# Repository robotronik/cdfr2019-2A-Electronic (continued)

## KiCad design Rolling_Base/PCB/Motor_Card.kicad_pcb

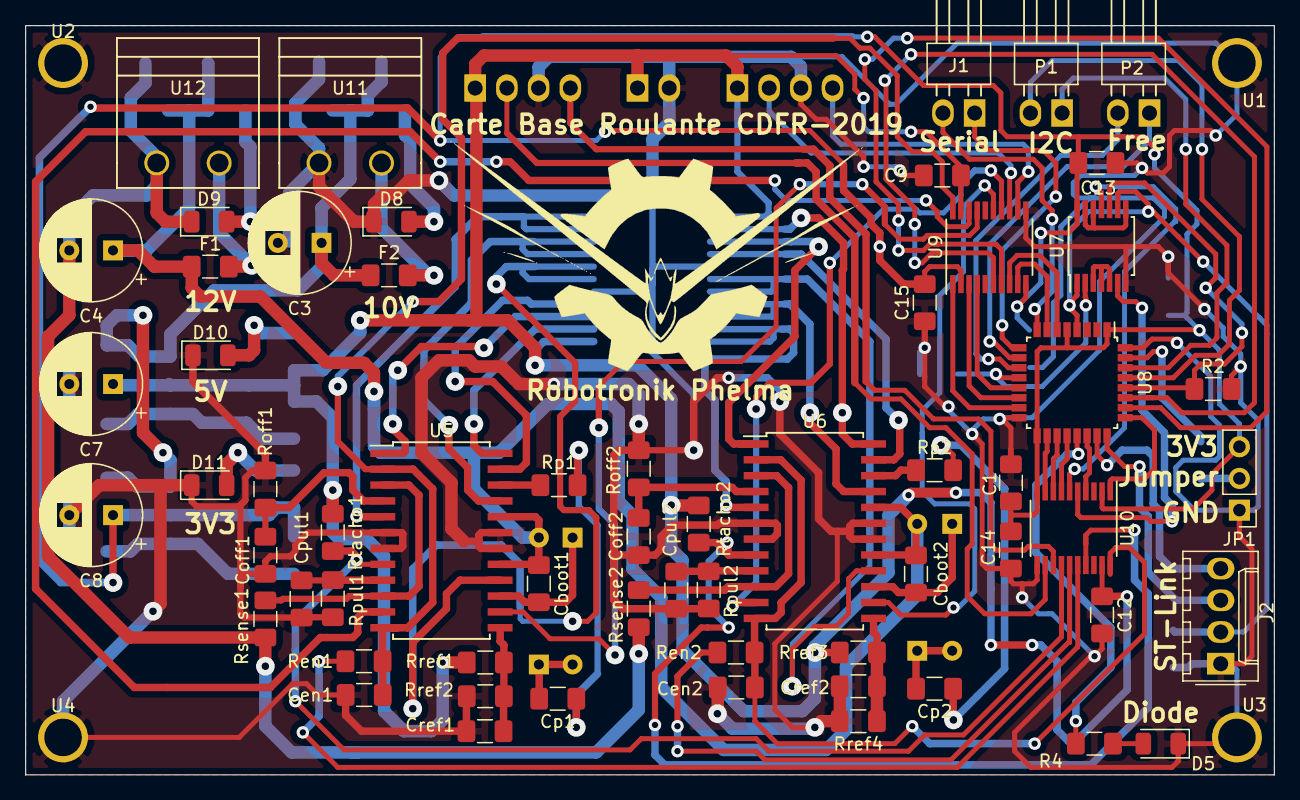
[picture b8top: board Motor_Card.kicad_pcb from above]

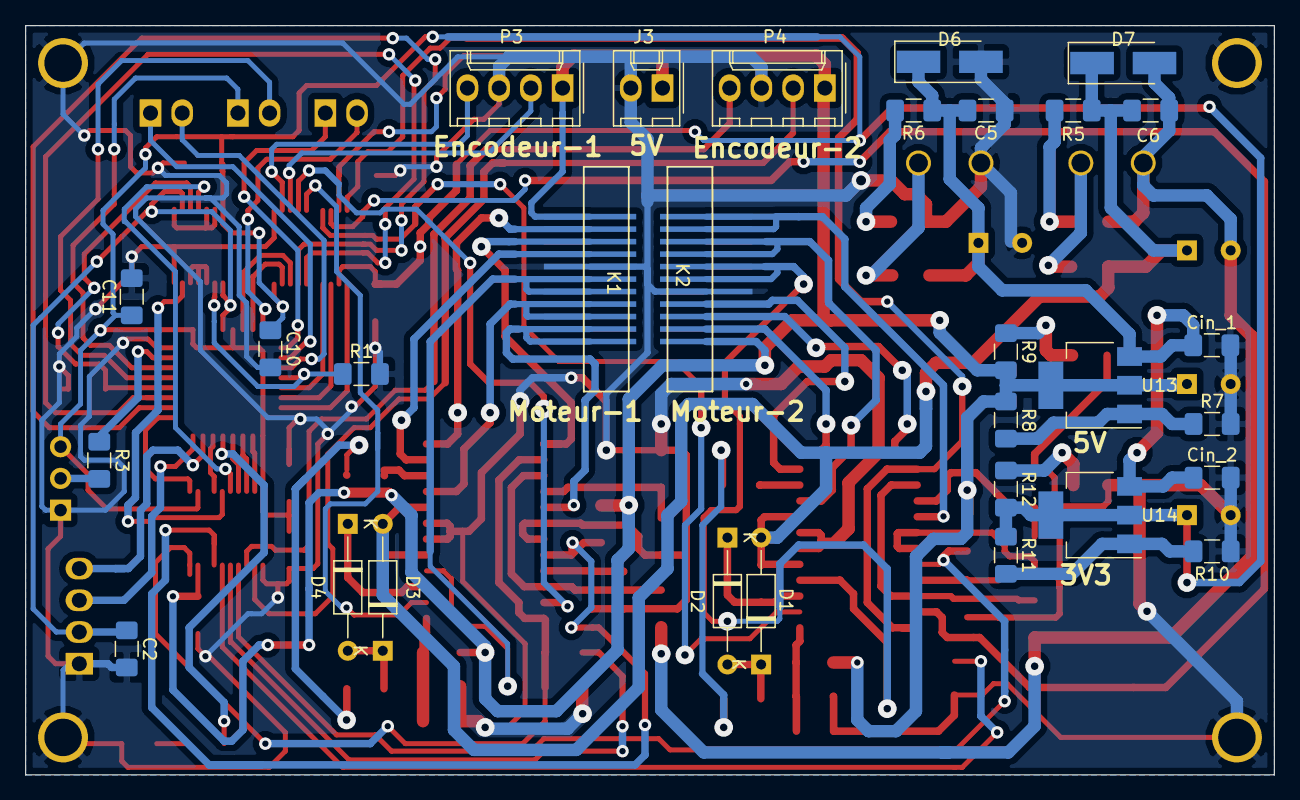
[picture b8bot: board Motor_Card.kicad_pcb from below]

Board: 2 copper layers, 100.0 x 60.0 mm, 94 parts (30 on the bottom side), 87 nets.

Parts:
C1, C2, C5, C6, C13, C14, C15: 100n; C_1206_3216Metric_Pad1.42x1.75mm_HandSolder
C3, C4: 100u; CP_Radial_D8.0mm_P3.50mm
C7, C8: 10u; CP_Radial_D8.0mm_P3.50mm
C9, C10, C11, C12: 0,1u; C_1206_3216Metric_Pad1.42x1.75mm_HandSolder
Cboot1, Cboot2: 220n; C_1206_3216Metric_Pad1.42x1.75mm_HandSolder
Cen1, Cen2: 5.6n; C_1206_3216Metric_Pad1.42x1.75mm_HandSolder
Cin_1, Cin_2: 0,1u; C_1206_3216Metric_Pad1.42x1.75mm_HandSolder
Coff1, Coff2: 1n; C_1206_3216Metric_Pad1.42x1.75mm_HandSolder
Cp1, Cp2: 10n; C_1206_3216Metric_Pad1.42x1.75mm_HandSolder
Cpul1, Cpul2: 10n; C_1206_3216Metric_Pad1.42x1.75mm_HandSolder
Cref1, Cref2: 10n; C_1206_3216Metric_Pad1.42x1.75mm_HandSolder
D1, D2, D3, D4: 1N4148; D_DO-35_SOD27_P10.16mm_Horizontal
D5, D9: LED_ALT; LED_1206_3216Metric
D6, D7: D_10A; D_SMA_Handsoldering
D8: LED_VCC; LED_1206_3216Metric
D10: LED_5V; LED_1206_3216Metric
D11: LED_3.3V; LED_1206_3216Metric
F1: Fuse_Puiss; Fuse_1206_3216Metric_Pad1.42x1.75mm_HandSolder
F2: Fuse_Num; Fuse_1206_3216Metric_Pad1.42x1.75mm_HandSolder
J1: CONN_SERIAL; Molex_KK-254_1x02_P2.54mm_Horizontal
J2: swdio; Molex_KK-254_AE-6410-04A_1x04_P2.54mm_Vertical
J3: FAN; Molex_KK-254_AE-6410-02A_1x02_P2.54mm_Vertical
JP1: Jumper_NC_Dual; PinHeader_1x03_P2.54mm_Vertical
K1, K2: Maxon-200142; Molex-52610-1133
P1: CONN_I2C; Molex_KK-254_1x02_P2.54mm_Horizontal
P2: CONN_FREE; Molex_KK-254_1x02_P2.54mm_Horizontal
P3: encoder_1; Molex_KK-254_AE-6410-04A_1x04_P2.54mm_Vertical
P4: encoder_2; Molex_KK-254_AE-6410-04A_1x04_P2.54mm_Vertical
R1, R2, R3: 10k; R_1206_3216Metric_Pad1.42x1.75mm_HandSolder
R4, R9, R12: 470; R_1206_3216Metric_Pad1.42x1.75mm_HandSolder
R5, R6: 2k; R_1206_3216Metric_Pad1.42x1.75mm_HandSolder
R7: 820; R_1206_3216Metric_Pad1.42x1.75mm_HandSolder
R8: 270; R_1206_3216Metric_Pad1.42x1.75mm_HandSolder
R10: 370; R_1206_3216Metric_Pad1.42x1.75mm_HandSolder
R11: 220; R_1206_3216Metric_Pad1.42x1.75mm_HandSolder
Ren1, Ren2: 100k; R_1206_3216Metric_Pad1.42x1.75mm_HandSolder
Roff1, Roff2: 33k; R_1206_3216Metric_Pad1.42x1.75mm_HandSolder
Rp1, Rp2: 100; R_1206_3216Metric_Pad1.42x1.75mm_HandSolder
Rpul1, Rpul2: 47k; R_1206_3216Metric_Pad1.42x1.75mm_HandSolder
Rref1, Rref3: 1.2k; R_1206_3216Metric_Pad1.42x1.75mm_HandSolder
Rref2, Rref4: 220; R_1206_3216Metric_Pad1.42x1.75mm_HandSolder
Rsense1, Rsense2: 0.3; R_1206_3216Metric_Pad1.42x1.75mm_HandSolder
Rtacho1, Rtacho2: 1k; R_1206_3216Metric_Pad1.42x1.75mm_HandSolder
U1, U2, U3, U4: Trou-3
U5, U6: L6235D; SOIC-24W_7.5x15.4mm_P1.27mm
U7: 74HC00; TSSOP-14_4.4x5mm_P0.65mm
U8: stm32f303k8t6; LQFP-32_7x7mm_P0.8mm
U9, U10: txb0108; TSSOP-20_4.4x6.5mm_P0.65mm
U11, U12: B_Plug_5mm; Bplug-5mm
U13, U14: LM317_SOT223; SOT-223-3_TabPin2

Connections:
+3V3: C1.2, C8.1, C10.1, C11.1, C13.1, C14.1, C15.2, JP1.3, R11.1, R12.2, U7.14, U8.1, U8.5, U8.17, U9.2, U9.10, U10.2, U10.10, U14.2
+5V: C7.1, C9.1, C12.1, J3.1, K1.11, K2.11, P3.1, P4.1, R8.1, R9.2, Rref1.1, Rref3.1, Rtacho1.1, Rtacho2.1, U9.19, U10.19, U13.2
+10V: C3.1, C5.1, Cin_1.1, Cin_2.1, D6.1, F2.1, R6.2, U13.3, U14.3
+12V: C4.1, C6.1, Cboot1.1, Cboot2.1, D1.2, D3.2, D7.1, F1.1, R5.2, U5.17, U5.20, U6.17, U6.20
/encodeurs/Ch_A1: U8.6, U9.8
/encodeurs/Ch_A1(+5V): P3.2, U9.13
/encodeurs/Ch_A2: U8.18, U10.9
/encodeurs/Ch_A2(+5V): P4.2, U10.12
/encodeurs/Ch_B1: U8.7, U9.9
/encodeurs/Ch_B1(+5V): P3.4, U9.12
/encodeurs/Ch_B2: U8.19, U10.8
/encodeurs/Ch_B2(+5V): P4.4, U10.13
/motor_part/BRAKE_1: U5.14, U9.17
/motor_part/BRAKE_2: U6.14, U9.15
/motor_part/DIAG_1: Cen1.2, Ren1.2, U5.2, U5.12, U9.20
/motor_part/DIAG_2: Cen2.2, Ren2.2, U6.2, U6.12, U10.20
/motor_part/DIR_1: U5.11, U9.18
/motor_part/DIR_2: U6.11, U9.14
/motor_part/EN_1: Ren1.1, U10.16
/motor_part/EN_2: Ren2.1, U10.15
/motor_part/Hall_sensor_11: K1.9, U5.1
/motor_part/Hall_sensor_12: K2.9, U6.1
/motor_part/Hall_sensor_21: K1.8, U5.23
/motor_part/Hall_sensor_22: K2.8, U6.23
/motor_part/Hall_sensor_31: K1.10, U5.24
/motor_part/Hall_sensor_32: K2.10, U6.24
/motor_part/Out_11: K1.1, K1.2, U5.5
/motor_part/Out_12: K2.1, K2.2, U6.5
/motor_part/Out_21: K1.3, K1.4, U5.21
/motor_part/Out_22: K2.3, K2.4, U6.21
/motor_part/Out_31: K1.5, K1.6, U5.16
/motor_part/Out_33: K2.5, K2.6, U6.16
/motor_part/TACHO_1: Rtacho1.2, U5.8, U10.14
/motor_part/TACHO_2: Rtacho2.2, U6.8, U10.17
/power_part/Alim_num: F2.2, U11.1
/power_part/Alim_puiss: F1.2, U12.1
/uC/Brake_1(3V3): U8.13, U9.4
/uC/Brake_2(3V3): U8.27, U9.6
/uC/Cmd_En_1(3V3): R1.1, U7.2, U8.12
/uC/Cmd_En_2(3V3): R2.1, U7.10, U8.28
/uC/Diag_1(3V3): U8.15, U9.1
/uC/Diag_2(3V3): U8.25, U10.1
/uC/Dir_1(3V3): U8.14, U9.3
/uC/Dir_2(3V3): U8.26, U9.7
/uC/Free_1(3V3): P2.1, U8.10
/uC/Free_2(3V3): P2.2, U8.11
/uC/I2C_SCL(3V3): P1.2, U8.29
/uC/I2C_SDA(3V3): P1.1, U8.30
/uC/RX(3V3): J1.1, U8.9
/uC/TX(3V3): J1.2, U8.8
/uC/Tacho_1(3V3): U8.20, U10.7
/uC/Tacho_2(3V3): U8.22, U10.4
/uC/nrst(3V3): C2.1, J2.2, U7.1, U7.9, U8.4
/uC/swclk(3V3): J2.3, U8.24
/uC/swdio(3V3): J2.4, U8.23
GND: C1.1, C2.2, C3.2, C5.2, C7.2, C8.2, C9.2, C10.2, C11.2, C12.2, C13.2, C14.2, C15.1, Cen1.1, Cen2.1, Cin_1.2, Cin_2.2, Coff1.1, Coff2.1, Cpul1.1, Cpul2.1, Cref1.2, Cref2.2, D5.1, D6.2, D8.1, D10.1, D11.1, J2.1, J3.2, JP1.1, K1.7, K2.7, P3.3, P4.3, R1.2, R2.2, R7.2, R10.1, Roff1.1, Roff2.1, Rpul1.1, Rpul2.1, Rref2.2, Rref4.2, U1.1, U2.1, U3.1, U4.1, U5.6, U5.7, U5.18, U5.19, U6.6, U6.7, U6.18, U6.19, U7.7, U8.16, U8.32, U9.11, U10.11, U11.2
GNDPWR: C4.2, C6.2, D7.2, D9.1, Rsense1.2, Rsense2.2, U12.2
unnamed: Cboot1.2, D2.1, U5.15
unnamed: Cboot2.2, D4.1, U6.15
unnamed: Coff1.2, Roff1.2, U5.4
unnamed: Coff2.2, Roff2.2, U6.4
unnamed: Cp1.1, Rp1.2
unnamed: Cp1.2, D1.1, D2.2
unnamed: Cp2.1, Rp2.2
unnamed: Cp2.2, D3.1, D4.2
unnamed: Cpul1.2, Rpul1.2, U5.9
unnamed: Cpul2.2, Rpul2.2, U6.9
unnamed: Cref1.1, Rref1.2, Rref2.1, U5.13
unnamed: Cref2.1, Rref3.2, Rref4.1, U6.13
unnamed: D5.2, R4.2
unnamed: D8.2, R6.1
unnamed: D9.2, R5.1
unnamed: D10.2, R9.1
unnamed: D11.2, R12.1
unnamed: JP1.2, R3.2
unnamed: R3.1, U8.31
unnamed: R4.1, U8.21
unnamed: R7.1, R8.2, U13.1
unnamed: R10.2, R11.2, U14.1
unnamed: Rp1.1, U5.22
unnamed: Rp2.1, U6.22
unnamed: Rsense1.1, U5.3, U5.10
unnamed: Rsense2.1, U6.3, U6.10
unnamed: U7.3, U7.4, U7.5
unnamed: U7.8, U7.12, U7.13
unnamed: U7.6, U10.5
unnamed: U7.11, U10.6

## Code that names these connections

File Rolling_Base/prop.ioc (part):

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Mcu.Name=STM32F303K(6-8)Tx
Mcu.Package=LQFP32
Mcu.UserName=STM32F303K8Tx
PA0.Signal=S_TIM2_CH1_ETR
PA1.Signal=S_TIM2_CH2
PA10.GPIOParameters=GPIO_Label
PA10.GPIO_Label=TACHO_1
PA10.Signal=GPIO_Input
PA11.GPIOParameters=GPIO_Label
PA11.GPIO_Label=LED
PA11.Signal=GPIO_Output
PA12.GPIOParameters=GPIO_Label
PA12.GPIO_Label=TACHO_2
PA12.Signal=GPIO_Input
PA15.GPIOParameters=GPIO_Label
PA15.GPIO_Label=DIAG_2
PA15.Signal=GPIO_Input
PA2.Mode=Asynchronous
PA2.Signal=USART2_TX
PA3.Mode=Asynchronous
PA3.Signal=USART2_RX
PA6.GPIOParameters=GPIO_Label
PA6.GPIO_Label=EN_1
PA6.Signal=S_TIM16_CH1
PA7.GPIOParameters=GPIO_Label
PA7.GPIO_Label=BRAKE_1
PA7.Signal=S_TIM3_CH2
PA8.Signal=S_TIM1_CH1
PA9.Signal=S_TIM1_CH2
PB0.GPIOParameters=GPIO_Label
PB0.GPIO_Label=DIR_1
PB0.Signal=GPIO_Output
PB1.GPIOParameters=GPIO_Label
PB1.GPIO_Label=DIAG_1
PB1.Signal=GPIO_Input
PB3.GPIOParameters=GPIO_Label
PB3.GPIO_Label=DIR_2
PB3.Signal=GPIO_Output
PB4.GPIOParameters=GPIO_Label
PB4.GPIO_Label=BRAKE_2
PB4.Signal=S_TIM3_CH1
PB5.GPIOParameters=GPIO_Label
PB5.GPIO_Label=EN_2
PB5.Signal=S_TIM17_CH1
PB6.Mode=I2C
PB6.Signal=I2C1_SCL
PB7.Mode=I2C
PB7.Signal=I2C1_SDA
RCC.HSEPLLFreq_Value=8000000
RCC.HSE_VALUE=8000000
RCC.SYSCLKFreq_VALUE=64000000
RCC.SYSCLKSourceVirtual=RCC_SYSCLKSOURCE_PLLCLK

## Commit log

2019-03-17 Update of the Repository
2019-03-17 End of the schematic
2019-03-18 First big step in route
2019-03-18 End of the route step
2019-03-19 Debug of route part + 3dshapes
2019-03-19 Add of the 3D file in .step in the folder
2019-03-22 Power card
2019-05-13 Add electronic from 3A
2019-05-18 update encoder level shifter
2019-10-03 modif de la carte d'adaptation pour les moteurs
2019-10-03 carte commande moteur brushless
2019-10-22 nouvelle version de la carte d'adaptation des connecteurs moteurs
2019-10-24 modif driver brushless
2019-10-25 modif driver moteur
2019-11-14 driver brushless
2019-11-27 modif du PCB driver_brushless
2019-12-05 Ajout du dossier phare et le cahier de suivi du projet
2019-12-06 Ajout du dossier phare et cahier de suivi du projet
2019-12-14 Déplacement du dossier phare
2020-01-23 programme pour tracer un graphe à partir de données envoyées par une STM32
2020-01-23 afficheSerieGraphe
2020-01-23 test
2020-01-23 afficheGrapheSerie
2020-02-21 afficheGrapheSerie : création de fichiers .c .h séparés
2020-02-29 ajout de la possibilité d'afficher les courbes dans plusieurs fenêtres
2020-04-21 ajout d'une petite doc pour afficheGrapheSerie
